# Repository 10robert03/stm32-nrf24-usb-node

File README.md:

# STM32-nRF24 Wireless USB Node

A compact 2-layer PCB featuring an **STM32C011** microcontroller and an **nRF24L01+** 2.4GHz wireless transceiver. This project was designed to bridge the gap between custom wireless sensor networks and USB-enabled host systems.

**⚠️ Project Status:** This project is currently in the **Hardware Prototype** stage. The PCB layout is complete, but the board has not yet been fully assembled or laboratory tested. Use with caution for production environments.

## Technical Highlights
- **Microcontroller:** STM32C011 (Arm Cortex-M0+), chosen for its efficiency and compact form factor.
- **Wireless Interface:** nRF24L01+ module connector, providing low-power 2.4GHz communication via SPI.
- **USB-UART Bridge:** Integrated **MCP2200** for seamless serial debugging and data acquisition.
- **Power Management:** Supports wide input voltage (5V - 36V) via **TSR 0.5-2433** DC/DC buck regulator.
  - Reverse polarity protection via Schottky diode.
  - Decoupled USB-C port (Data only) to prevent VBUS conflicts with host devices.

## Engineering Lessons & Design Choices

During the development of this board, several critical hardware engineering principles were implemented to ensure stability and signal integrity:

### 1. High-Frequency Signal Integrity
* **Series Termination:** Integrated series resistors on high-speed lines to dampen ringing and control rise/fall times. This minimizes electromagnetic interference (EMI) and prevents signal reflections.
* **Impedance Control:** Careful routing of USB D+/D- differential pairs to maintain signal quality for the MCP2200 bridge.

### 2. Clock & Timing Precision
* **Independent Oscillators:** Implemented separate external crystals for the STM32 (8 MHz) and MCP2200 (12 MHz). 
* **Parasitic Optimization:** Load capacitors were placed in immediate proximity to the crystals to minimize parasitic inductance and ensure a stable startup of the oscillation.

### 3. Power Integrity & Noise Suppression
* **Decoupling Strategy:** Strategic placement of ceramic decoupling capacitors (100nF) directly at the VCC pins of each IC to provide local energy storage and filter high-frequency switching noise.
* **RF-Sensitive Filtering:** Added LC-filtering stages at the output of the switching regulator to provide a "clean" 3.3V rail for the nRF24L01+, which is highly sensitive to power supply ripple.

### 4. Advanced PCB Layout Techniques
* **Tight Component Placement:** Mastered the challenge of placing high-pin-count components (USB-C, STM32, MCP2200) in a very confined space while maintaining minimum clearance for the Ground Plane (GND).
* **Thermal Management:** Solid Ground Fill on the bottom layer acts as a heat sink and provides a low-impedance return path for all signals.

##  Project Structure
- `/Screenshots`: High-resolution renders, schematic snips, and hardware photos.
- `stm32c_nrf.kicad_pcb`: The 2-layer board layout.
- `stm32c_nrf.kicad_sch`: The full electrical schematic.

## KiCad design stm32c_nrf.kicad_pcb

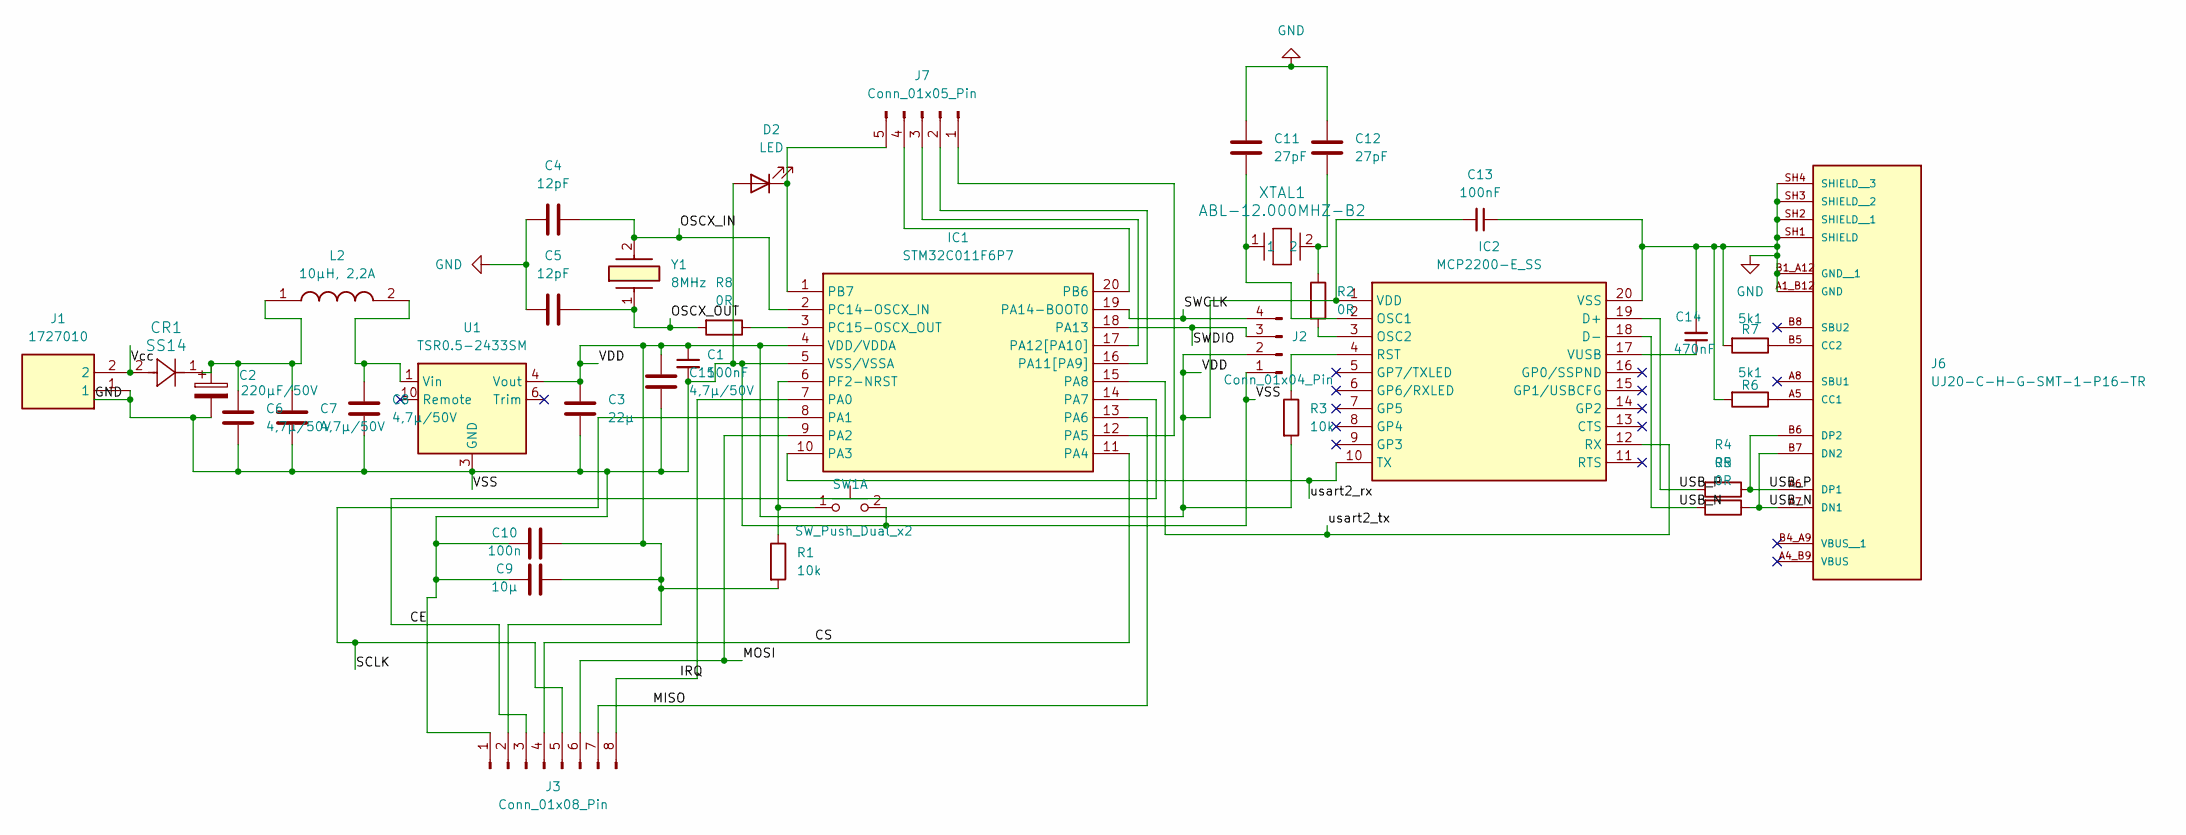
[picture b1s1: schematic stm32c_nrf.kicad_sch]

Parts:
C1, C13: 100nF; C_0805_2012Metric_Pad1.18x1.45mm_HandSolder
C2: 220µF/50V; Cap_Elec_6,2_3,3
C3: 22µ; C_0805_2012Metric_Pad1.18x1.45mm_HandSolder
C4, C5: 12pF; C_0805_2012Metric
C6, C7, C8, C15: 4,7µ/50V; C_0805_2012Metric_Pad1.18x1.45mm_HandSolder
C9: 10µ; C_0805_2012Metric_Pad1.18x1.45mm_HandSolder
C10: 100n; C_0805_2012Metric_Pad1.18x1.45mm_HandSolder
C11, C12: 27pF; C_0805_2012Metric_Pad1.18x1.45mm_HandSolder
C14: 470nF; C_0805_2012Metric_Pad1.18x1.45mm_HandSolder
CR1: SS14; CR_SMA_403AE_OSI
D2: LED; LED_0805_2012Metric
IC1: STM32C011F6P7; SOP65P640X120-20N; Manufacturer_Part_Number STM32C011F6P7; Mouser Part Number 511-STM32C011F6P7
IC2: MCP2200-E_SS; SOP65P780X200-20N; Mouser Part Number 494-MCP2200-E/SS
J1: 1727010; Mouser Part Number 651-1727010
J2: Conn_01x04_Pin; PinHeader_1x04_P2.00mm_Vertical
J3: Conn_01x08_Pin; nRF24L01_Breakout
J6: UJ20-C-H-G-SMT-1-P16-TR; SAMESKY_UJ20-C-H-G-SMT-1-P16-TR; PARTREV 1.0
J7: Conn_01x05_Pin; PinHeader_1x05_P2.00mm_Vertical
L2: 10µH, 2,2A; WE-PD2_5848_582055; Mouser Part Number 710-74477410
R1, R3: 10k; R_0805_2012Metric_Pad1.20x1.40mm_HandSolder
R2, R4, R5, R8: 0R; R_0805_2012Metric_Pad1.20x1.40mm_HandSolder
R6, R7: 5k1; R_0805_2012Metric_Pad1.20x1.40mm_HandSolder
SW1: SW_Push_Dual_x2; SW_TH_Tactile_Omron_B3F-100x
U1: TSR0.5-2433SM; Converter_DCDC_TRACO_TSR0.5-24xxSM_241xxSM_SMD
XTAL1: ABL-12.000MHZ-B2; XTAL_ABL_ABR
Y1: 8MHz; HC49SDLF800MHZ; Manufacturer_Part_Number HC49SDLF-8.00MHZ

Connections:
/CE: IC1.14 (PA7), J3.3
/CS: IC1.11 (PA4), J3.4
/IRQ: IC1.7 (PA0), J3.8
/MISO: IC1.13 (PA6), J3.7
/MOSI: IC1.9 (PA2), J3.6
/OSCX_IN: C4.2, IC1.2 (PC14-OSCX_IN), Y1.2
/OSCX_OUT: C5.2, R8.2, Y1.1
/SCLK: IC1.8 (PA1), J3.5
/SWCLK: IC1.19 (PA14-BOOT0), J2.4
/SWDIO: IC1.18 (PA13), J2.3
/USB_N: IC2.18 (D-), J6.A7 (DN1), J6.B7 (DN2), R5.1, R5.2
/USB_P: IC2.19 (D+), J6.A6 (DP1), J6.B6 (DP2), R4.1, R4.2
/VDD: C1.1, C3.1, C9.1, C10.1, C13.2, C15.1, IC1.4 (VDD/VDDA), IC2.1 (VDD), J2.2, J3.2, R1.2, R3.2, U1.4 (Vout), U1.5 (Vout)
/Vcc: CR1.2, J1.2
/usart2_rx: IC1.10 (PA3), IC2.10 (TX)
/usart2_tx: IC1.15 (PA8), IC2.12 (RX)
GND: C1.2, C2.2, C3.2, C4.1, C5.1, C6.2, C7.2, C8.2, C9.2, C10.2, C11.1, C12.1, C13.1, C14.2, C15.2, D2.2 (A), IC1.5 (VSS/VSSA), IC2.20 (VSS), J1.1, J2.1, J3.1, J6.A1_B12 (GND), J6.B1_A12 (GND__1), J6.SH1 (SHIELD), J6.SH2 (SHIELD__1), J6.SH3 (SHIELD__2), J6.SH4 (SHIELD__3), R6.2, R7.2, SW1.2 (D), U1.3 (GND), U1.7 (GND), U1.8 (GND), U1.9 (GND)
unnamed: C2.1, C6.1, C7.1, CR1.1, L2.1
unnamed: C8.1, L2.2, U1.1 (Vin), U1.2 (Vin)
unnamed: C12.2, R2.1, XTAL1.2
unnamed: D2.1 (K), IC1.1 (PB7), J7.5
unnamed: IC1.12 (PA5), J7.1
unnamed: IC1.16 (PA11[PA9]), J7.2
unnamed: IC1.17 (PA12[PA10]), J7.3
unnamed: IC1.20 (PB6), J7.4
unnamed: IC1.3 (PC15-OSCX_OUT), R8.1
unnamed: IC1.6 (PF2-NRST), R1.1, SW1.1 (C)
unnamed: C11.2, IC2.2 (OSC1), XTAL1.1
unnamed: IC2.3 (OSC2), R2.2
unnamed: IC2.4 (RST), R3.1
unnamed: C14.1, IC2.17 (VUSB)
unnamed: J6.A5 (CC1), R6.1
unnamed: J6.B5 (CC2), R7.1

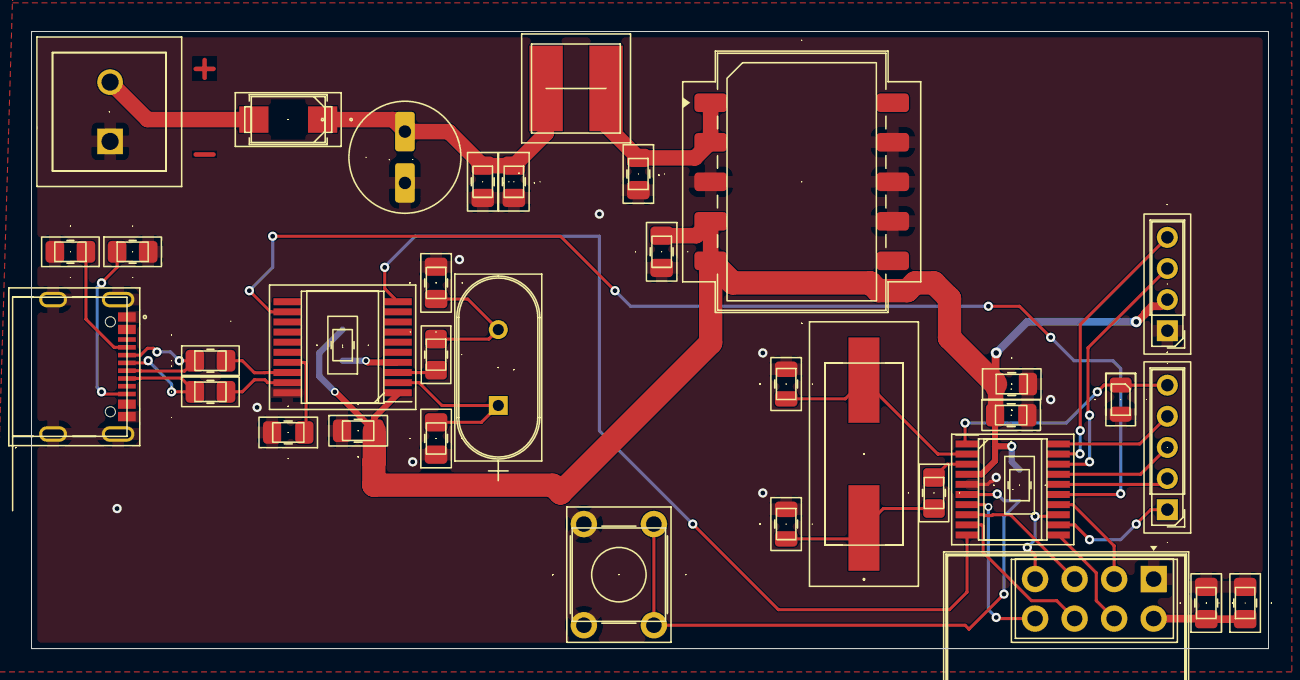
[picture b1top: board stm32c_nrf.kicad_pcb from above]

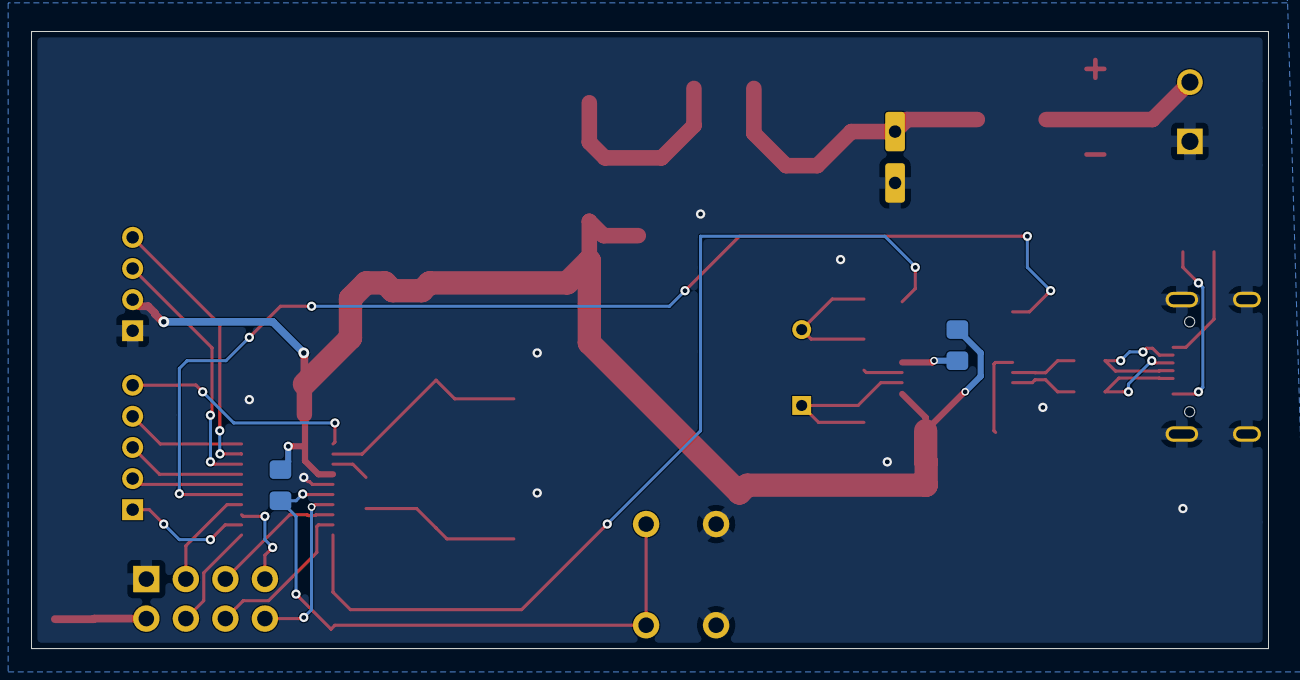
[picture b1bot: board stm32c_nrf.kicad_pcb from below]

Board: 2 copper layers, 79.5 x 39.7 mm, 37 parts (2 on the bottom side), 33 nets.

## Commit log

2026-05-14 Revise README with detailed project information
    Expanded project description and added technical highlights, engineering lessons, and project structure details.
